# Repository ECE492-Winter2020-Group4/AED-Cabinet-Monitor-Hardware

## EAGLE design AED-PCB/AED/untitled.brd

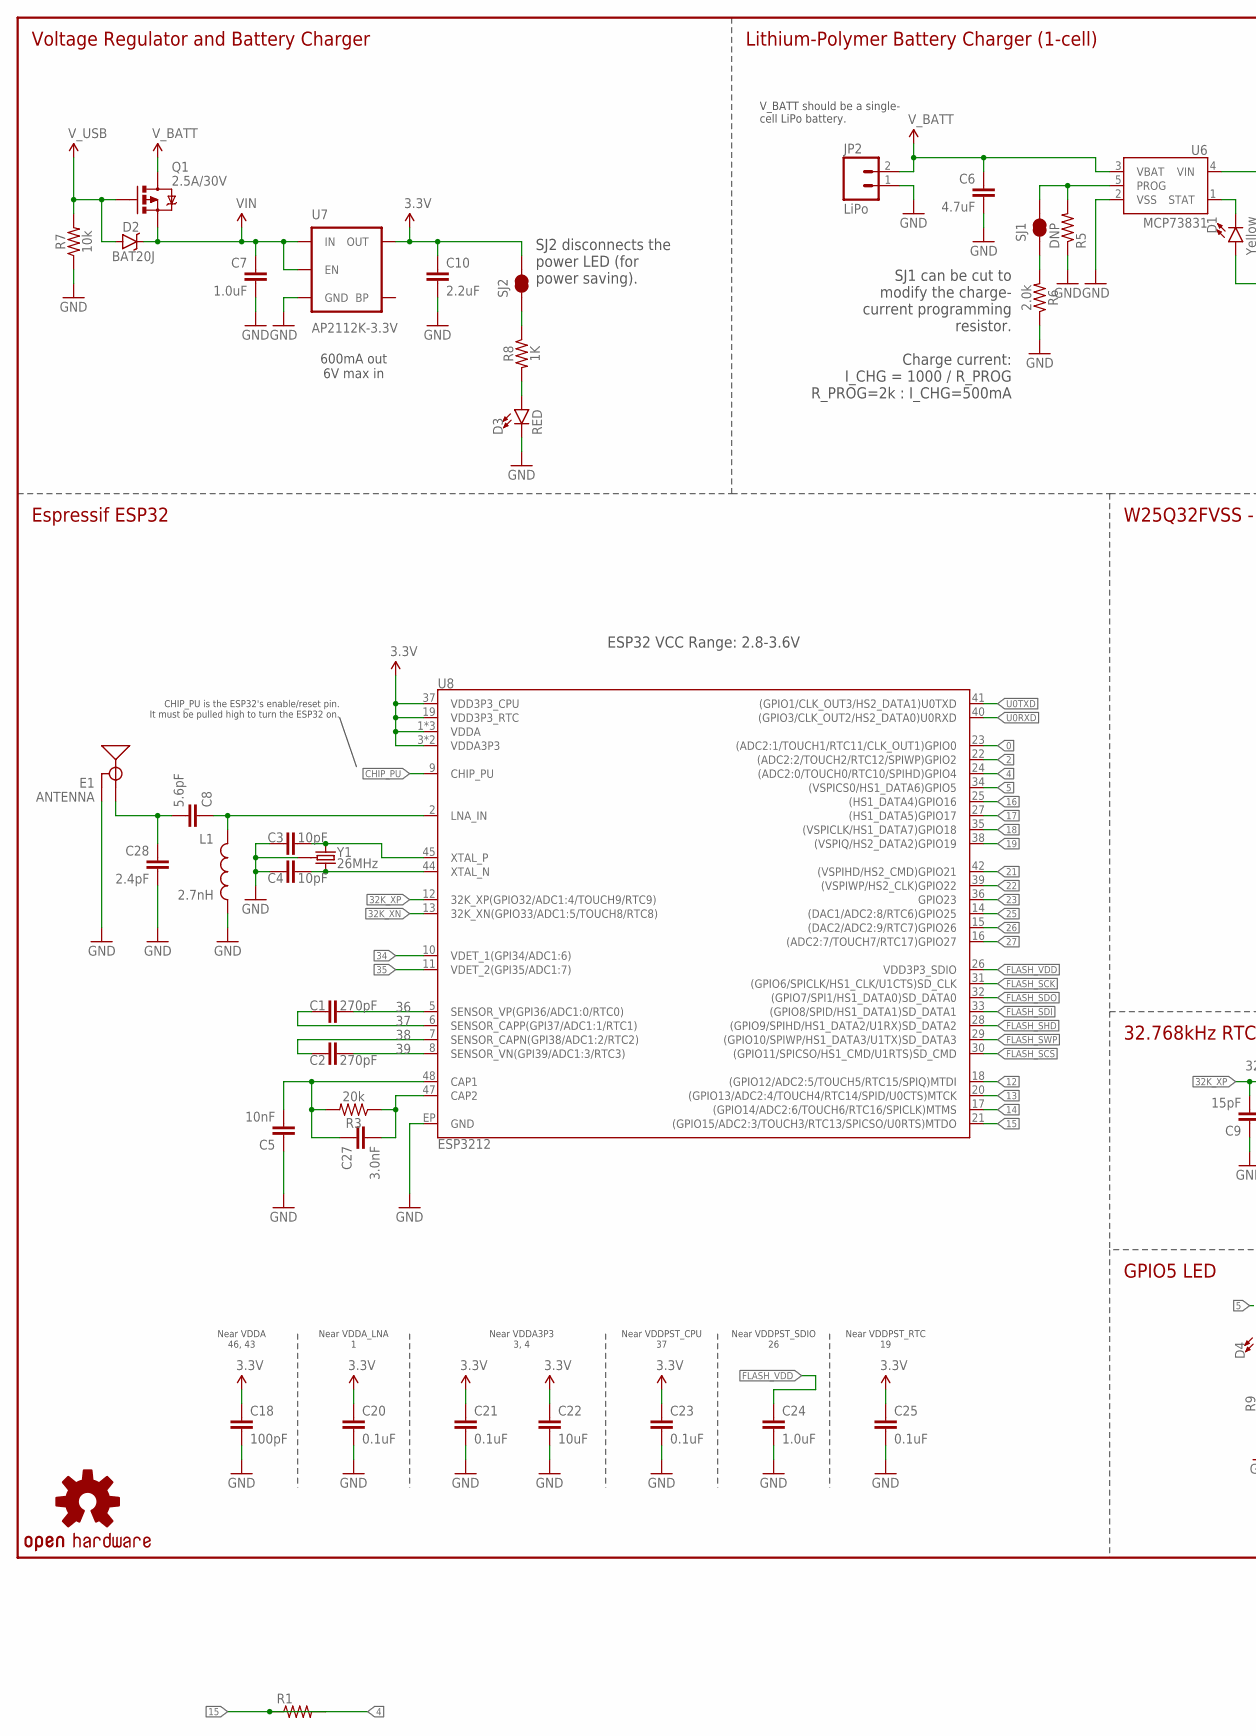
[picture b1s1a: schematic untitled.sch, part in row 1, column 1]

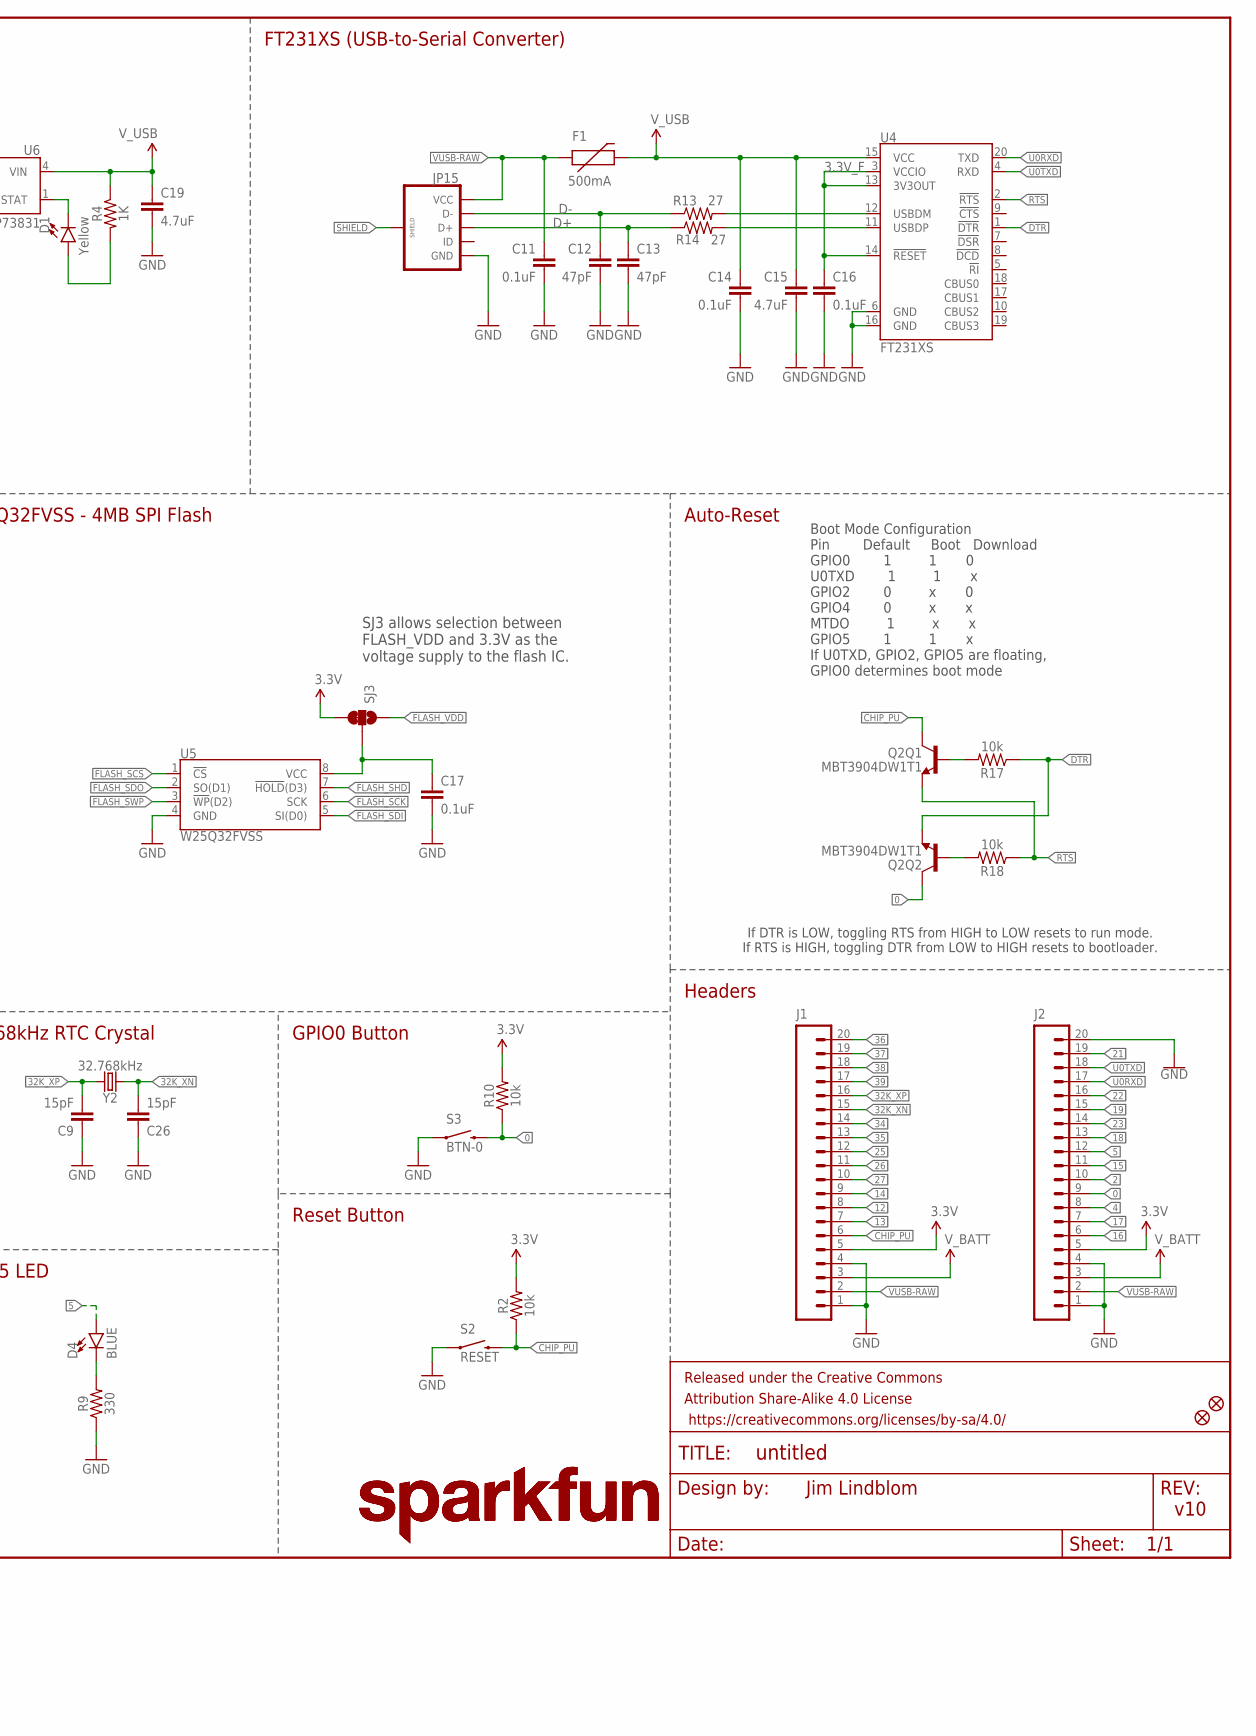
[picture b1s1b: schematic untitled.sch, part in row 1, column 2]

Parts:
C1, C2: 270pF; 0603
C3, C4: 10pF; 0603
C5: 10nF; 0603
C6, C19: 4.7uF; 0603
C7: 1.0uF; 0805
C8: 5.6pF; 0603
C9, C26: 15pF; 0603
C10: 2.2uF; 0603
C11, C14, C16, C17, C20, C21, C23, C25: 0.1uF; 0603
C12, C13: 47pF; 0603
C15: 4.7uF; 0603-CAP
C18: 100pF; 0603
C22: 10uF; 0603
C24: 1.0uF; 0603
C27: 3.0nF; 0603
C28: 2.4pF; 0603
D1: Yellow; LED-0603
D2: BAT20J; SOD-323
D3: RED; LED-0603
D4: BLUE; LED-0603
E1: ANTENNA; TRACE_ANTENNA_2.4GHZ_25.7MM_TUNED
F1: 500mA; PTC-1206
FD1, FD2: FIDUCIALUFIDUCIAL; MICRO-FIDUCIAL
FRAME2: FRAME-LEDGER; CREATIVE_COMMONS
J1, J2: M20NOSILK; 1X20_NOSILK
JP2: LiPo; JST-2-PTH
JP15: USB_MICROB_PLUGCONN-11752; USB-B-MICRO-SMD_V03
L1: 2.7nH; 0603
LOGO1, LOGO3: SFE_LOGO_NAME.2_INCH; SFE_LOGO_NAME_.2
LOGO2: OSHW-LOGOMINI; OSHW-LOGO-MINI
Q1: 2.5A/30V; SOT23-3
Q2: MBT3904DW1T1; SC70-6
R1: R-US_M0805; M0805
R2, R7, R10, R17, R18: 10k; 0603
R3: 20k; 0603
R4, R8: 1K; 0603
R5: DNP; 1/6W-RES
R6: 2.0k; 0603
R9: 330; 0603
R13, R14: 27; 0603
S2: RESET; TACTILE_SWITCH_SMD_4.6X2.8MM
S3: BTN-0; TACTILE_SWITCH_SMD_4.6X2.8MM
SJ1, SJ2: JUMPER-PAD-2-NC_BY_TRACE; PAD-JUMPER-2-NC_BY_TRACE_YES_SILK
SJ3: JUMPER-PAD-3-2OF3_NC_BY_TRACE_SMALL; PAD-JUMPER-3-2OF3_NC_BY_TRACE_YES_SILK_FULL_BOX
U4: FT231XS; SSOP20_L
U5: W25Q32FVSS; SOIC-8
U6: MCP73831; SOT23-5
U7: AP2112K-3.3V; SOT23-5
U8: ESP3212; QFN48-0.4MM
Y1: 26MHz; CRYSTAL-SMD-3.2X2.5
Y2: 32.768kHz; CRYSTAL-SMD-3.2X1.5MM

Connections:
0: J2.9, Q2.6 (C), R10.1, S3.3 (2), S3.4 (2), U8.23 ((ADC2:1/TOUCH1/RTC11/CLK_OUT1)GPIO0)
2: J2.10, U8.22 ((ADC2:2/TOUCH2/RTC12/SPIWP)GPIO2)
3.3V: C10.1, C18.1, C20.1, C21.1, C22.1, C23.1, C25.1, J1.5, J2.5, R2.2, R10.2, SJ2.2, SJ3.3, U7.5 (OUT), U8.1 (VDDA), U8.3 (VDDA3P3), U8.4 (VDDA3P3), U8.19 (VDD3P3_RTC), U8.37 (VDD3P3_CPU), U8.43 (VDDA), U8.46 (VDDA)
3.3V_F: C16.1, U4.3 (VCCIO), U4.13 (3V3OUT), U4.14 (!RESET)
4: J2.8, U8.24 ((ADC2:0/TOUCH0/RTC10/SPIHD)GPIO4)
5: D4.A, J2.12, U8.34 ((VSPICS0/HS1_DATA6)GPIO5)
12: J1.8, U8.18 ((GPIO12/ADC2:5/TOUCH5/RTC15/SPIQ)MTDI)
13: J1.7, U8.20 ((GPIO13/ADC2:4/TOUCH4/RTC14/SPID/U0CTS)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)
14: J1.9, U8.17 ((GPIO14/ADC2:6/TOUCH6/RTC16/SPICLK)MTMS)
15: J2.11, U8.21 ((GPIO15/ADC2:3/TOUCH3/RTC13/SPICSO/U0RT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)
16: J2.6, U8.25 ((HS1_DATA4)GPIO16)
17: J2.7, U8.27 ((HS1_DATA5)GPIO17)
18: J2.13, U8.35 ((VSPICLK/HS1_DATA7)GPIO18)
19: J2.15, U8.38 ((VSPIQ/HS2_DATA2)GPIO19)
21: J2.19, U8.42 ((VSPIHD/HS2_CMD)GPIO21)
22: J2.16, U8.39 ((VSPIWP/HS2_CLK)GPIO22)
23: J2.14, U8.36 (GPIO23)
25: J1.12, U8.14 ((DAC1/ADC2:8/RTC6)GPIO25)
26: J1.11, U8.15 ((DAC2/ADC2:9/RTC7)GPIO26)
27: J1.10, U8.16 ((ADC2:7/TOUCH7/RTC17)GPIO27)
32K_XN: C26.2, J1.15, U8.13 (32K_XN(GPIO33/ADC1:5/TOUCH8/RTC8)), Y2.P$2 (2)
32K_XP: C9.2, J1.16, U8.12 (32K_XP(GPIO32/ADC1:4/TOUCH9/RTC9)), Y2.P$1 (1)
34: J1.14, U8.10 (VDET_1(GPI34/ADC1:6))
35: J1.13, U8.11 (VDET_2(GPI35/ADC1:7))
36: C1.2, J1.20, U8.5 (SENSOR_VP(GPI36/ADC1:0/RTC0))
37: C1.1, J1.19, U8.6 (SENSOR_CAPP(GPI37/ADC1:1/RTC1))
38: C2.1, J1.18, U8.7 (SENSOR_CAPN(GPI38/ADC1:2/RTC2))
39: C2.2, J1.17, U8.8 (SENSOR_VN(GPI39/ADC1:3/RTC3))
CAP_10N: C5.2, C27.1, R3.2, U8.48 (CAP1)
CHIP_PU: J1.6, Q2.3 (C), R2.1, S2.3 (2), S2.4 (2), U8.9 (CHIP_PU)
D+: C13.1, JP15.D+, R14.1
D-: C12.1, JP15.D-, R13.1
DTR: Q2.1 (E), R17.1, U4.1 (!DTR)
FLASH_SCK: U5.6 (SCK), U8.31 ((GPIO6/SPICLK/HS1_CLK/U1CTS)SD_CLK)
FLASH_SCS: U5.1 (!CS!), U8.30 ((GPIO11/SPICSO/HS1_CMD/U1RTS)SD_CMD)
FLASH_SDI: U5.5 (SI(D0)), U8.33 ((GPIO8/SPID/HS1_DATA1)SD_DATA1)
FLASH_SDO: U5.2 (SO(D1)), U8.32 ((GPIO7/SPI1/HS1_DATA0)SD_DATA0)
FLASH_SHD: U5.7 (!HOLD!(D3)), U8.28 ((GPIO9/SPIHD/HS1_DATA2/U1RX)SD_DATA2)
FLASH_SWP: U5.3 (!WP!(D2)), U8.29 ((GPIO10/SPIWP/HS1_DATA3/U1TX)SD_DATA3)
FLASH_VDD: C24.1, SJ3.1, U8.26 (VDD3P3_SDIO)
GND: C3.1, C4.1, C5.1, C6.2, C7.2, C9.1, C10.2, C11.2, C12.2, C13.2, C14.2, C15.2, C16.2, C17.2, C18.2, C19.2, C20.2, C21.2, C22.2, C23.2, C24.2, C25.2, C26.1, C28.2, D3.C, E1.GND, E1.GND2 (GND), J1.1, J1.4, J2.1, J2.4, J2.20, JP2.1, JP15.GND, L1.2, R5.1, R6.1, R7.1, R9.1, S2.1, S2.2 (1), S3.1, S3.2 (1), U4.6 (GND), U4.16 (GND), U5.4 (GND), U6.2 (VSS), U7.2 (GND), U8.EP (GND), Y1.2 (GND), Y1.4 (GND)
LNA_IN: C8.1, L1.1, U8.2 (LNA_IN)
unnamed: R1.1, R1.2
unnamed: R13.2, U4.12 (USBDM)
unnamed: R14.2, U4.11 (USBDP)
unnamed: D1.C, U6.1 (STAT)
unnamed: Q2.5 (B), R17.2
unnamed: C17.1, SJ3.2, U5.8 (VCC)
unnamed: Q2.2 (B), R18.2
unnamed: C3.2, U8.45 (XTAL_P), Y1.1
unnamed: R5.2, SJ1.2, U6.5 (PROG)
unnamed: C4.2, U8.44 (XTAL_N), Y1.3 (2)
unnamed: R6.2, SJ1.1
unnamed: D1.A, R4.2
unnamed: D3.A, R8.2
unnamed: R8.1, SJ2.1
unnamed: D4.C, R9.2
unnamed: C27.2, R3.1, U8.47 (CAP2)
RTS: Q2.4 (E), R18.1, U4.2 (!RTS)
SHIELD: JP15.SHIELD1 (SHIELD), JP15.SHIELD2 (SHIELD), JP15.SHIELD3 (SHIELD)
TRACE_ANT: C8.2, C28.1, E1.ANT (SIGNAL)
U0RXD: J2.17, U4.20 (TXD), U8.40 ((GPIO3/CLK_OUT2/HS2_DATA0)U0RXD)
U0TXD: J2.18, U4.4 (RXD), U8.41 ((GPIO1/CLK_OUT3/HS2_DATA1)U0TXD)
VIN: C7.1, D2.C, Q1.2 (S), U7.1 (IN), U7.3 (EN)
VUSB-RAW: C11.1, F1.1, J1.2, J2.2, JP15.VBUS (VCC)
V_BATT: C6.1, J1.3, J2.3, JP2.2, Q1.3 (D), U6.3 (VBAT)
V_USB: C14.1, C15.1, C19.1, D2.A, F1.2, Q1.1 (G), R4.1, R7.2, U4.15 (VCC), U6.4 (VIN)

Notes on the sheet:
Boot Mode Configuration Pin Default Boot Download GPIO0 1 1 0 U0TXD 1 1 x GPIO2 0 x 0 GPIO4 0 x x MTDO 1 x x GPIO5 1 1 x If U0TXD, GPIO2, GPIO5 are floating, GPIO0 determines boot mode
FT231XS (USB-to-Serial Converter)
V_BATT should be a single- cell LiPo battery.
Charge current: I_CHG = 1000 / R_PROG R_PROG=2k : I_CHG=500mA
Voltage Regulator and Battery Charger
SJ1 can be cut to modify the charge- current programming resistor.
Lithium-Polymer Battery Charger (1-cell)
600mA out 6V max in
Auto-Reset
Near VDDA 46, 43
Near VDDA_LNA 1
Near VDDA3P3 3, 4
Near VDDPST_CPU 37
Near VDDPST_SDIO 26
Near VDDPST_RTC 19
Espressif ESP32
W25Q32FVSS - 4MB SPI Flash
32.768kHz RTC Crystal
GPIO0 Button
Reset Button
GPIO5 LED
Headers
v10
Jim Lindblom
ESP32 VCC Range: 2.8-3.6V
SJ3 allows selection between FLASH_VDD and 3.3V as the voltage supply to the flash IC.
SJ2 disconnects the power LED (for power saving).
If DTR is LOW, toggling RTS from HIGH to LOW resets to run mode. If RTS is HIGH, toggling DTR from LOW to HIGH resets to bootloader.
CHIP_PU is the ESP32's enable/reset pin. It must be pulled high to turn the ESP32 on.

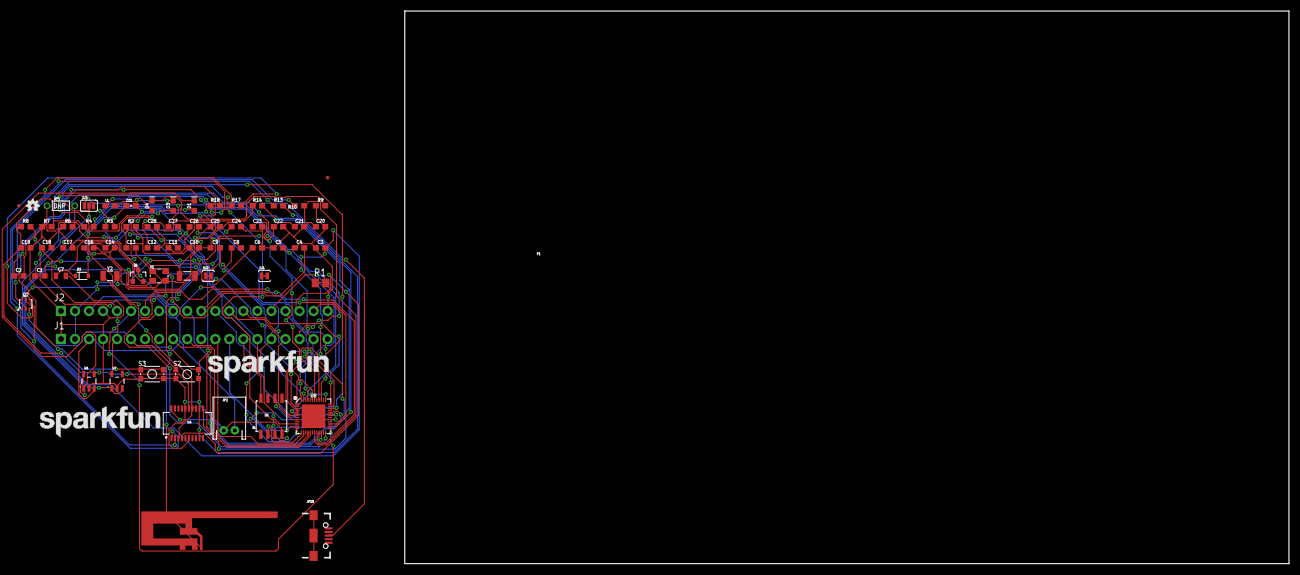
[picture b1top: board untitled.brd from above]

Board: 2 copper layers, 160.0 x 100.0 mm, 73 parts (0 on the bottom side), 67 nets.

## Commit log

2020-02-24 add project
2020-03-02 complete PCB
2020-03-02 complete PCB with the clear-up
2020-03-30 add case files and reorganise directories

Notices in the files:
parts and their libraries:
SparkFun-Capacitors: Licensing: Creative Commons ShareAlike 4.0 International - https://creativecommons.org/licenses/by-sa/4.0
SparkFun-Aesthetics: Released under the Creative Commons Attribution Share-Alike 4.0 License
SparkFun-Aesthetics: https://creativecommons.org/licenses/by-sa/4.0
